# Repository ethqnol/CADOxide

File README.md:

# CADoxide

**CADoxide** is a high-performance, open-core electronic design automation (EDA) and PCB CAD suite built from the ground up for modern hardware engineering. It combines a **100% Pure Rust WebAssembly frontend**, an **instanced WebGL2/GPU Signed Distance Field (SDF) graphics engine**, an **in-browser Design Rule Check (DRC) engine**, an **RS-274X Gerber & Excellon CAM exporter**, an **IPC-standard component footprint library**, and **geometric vector diffing**, with a **distributed Axum cloud backend** and a **Tauri v2 desktop core**.

All JavaScript/TypeScript and React layers have been eliminated: everything from streaming KiCad S-expression parsing, interactive track routing, via/pad placement, polygon zone rendering, real-time clearance rule verification, and CAM Gerber generation down to GPU draw dispatch and reactive DOM management runs in compiled, memory-safe native Rust and WebAssembly.

---

## Key Capabilities & Purpose

- **Interactive In-Browser & Desktop PCB CAD:**
  - Route tracks with 45° angle snapping, posture flipping (`/`), and interactive length tuning.
  - Place plated through-hole vias, pads, lines, arcs, circles, rectangles, text, and dimension callouts.
  - Define, preview, and render filled copper zones, thermal reliefs, and keepouts with customizable fill modes.
  - Configurable grid snapping ($0.05\text{ mm}$ to $2.54\text{ mm}$, mils, inches) with relative coordinate origins (`Space`) and dual Cartesian/polar HUD readouts.
- **Single-Draw-Call Instanced GPU SDF Engine:**
  - Renders entire complex multi-layer boards (traces, pads, zones, silkscreen, mask, holes) in a single instanced WebGL2 draw call.
  - Sub-pixel vertex-stage Level-of-Detail (LOD) and hardware frustum culling yielding silky-smooth 60+ FPS navigation over boards with 100k+ primitives.
  - Real-time 3D exploded multi-layer stackup orbit mode with true physical Z-height layer separation.
  - Instant GPU net highlighting and impedance/delay signal length probing across all copper layers.
- **Native In-Browser DRC Engine:**
  - Runs deep geometric clearance, minimum track width, drill hole clearance, short-circuit, and unconnected net audits directly in client-side Rust WebAssembly.
  - Visual error markers on the canvas with click-to-focus camera navigation and rule severity filtering.
- **RS-274X Gerber & Excellon Drill CAM Exporter:**
  - Client-side production-grade Gerber export for all copper, silkscreen, and solder mask layers (with automatic pad expansion aperture calculation) alongside standard NC Excellon drill files.
- **Built-in IPC Standard Footprint & Component Library:**
  - Ready-to-place standard SMD and THT footprints (0402, 0603, 0805, 1206 passives, SOT-23, SOIC-8, TSSOP-16, QFP-48, QFN-32, USB-C, 0.1" headers) with live SVG preview generator and automatic reference designator incrementing.
- **Hardware Collaboration, Vector Diffing & Review:**
  - Spatial quantized geometric diffing between PCB revisions ($R_A$ vs. $R_B$) with color-coded additions/removals and interactive split-wipe slider inspection.
  - Persistent redline review pins, threaded annotations, and synchronized design reviews backed by SQLite / PostgreSQL.
- **Dual Deployment — Desktop Native & Cloud Platform:**
  - Run natively as a lightweight desktop application via **Tauri v2** with direct filesystem and OS `kicad-cli` integrations.
  - Deploy as a scalable, containerized cloud collaboration hub with Axum, Tokio worker pools, Content-Addressable Storage (CAS), PostgreSQL, Redis, and MinIO.
- **Content-Addressable Storage (CAS):** Hashes PCB file contents and caches rendered layer SVGs and DRC analysis in memory. Cache hits bypass `kicad-cli` execution entirely.
- **Worker Pool & Message Broker:** Compute jobs (DRC verification, PCB SVG rendering, 3D VRML model generation) are pushed to a Tokio `mpsc` channel and scheduled across a bounded `Semaphore` worker pool.
- **Centralized Component Library (`parts_library`):**
  - Manages Manufacturer Part Numbers (MPNs), footprints, symbols, lifecycle statuses (`ACTIVE`, `NRND`, `OBSOLETE`), and cached DigiKey/Mouser inventory and unit pricing.
  - Accessible via the **Parts & BOM** tab in the UI with instant search filtering.
- **Collaborative Redline Review Threads:**
  - Review pins dropped at precise board coordinates $(X, Y\text{ mm})$ persist to SQLite (`review_threads`, `review_messages`) and sync in real time across clients.
  - Supports marking threads as **Resolved / Open** and jumping the GPU camera directly to annotations or DRC violations.

---

## Repository Structure

```
CADoxide/
├── crates/
│   └── cadoxide-wasm/           # 100% Pure Rust WASM Frontend & GPU Shader Engine
│       ├── Cargo.toml           # Configured for wasm32-unknown-unknown (zero JS dependencies)
│       └── src/
│           ├── gl_renderer.rs   # WebGL2 Instanced SDF Engine, LOD culling, 3D orbit
│           ├── parser.rs        # KiCad S-expression parser, O(1) spatial grid, vector diff
│           ├── drc_engine.rs    # Client-side clearance, track width, & drill DRC audit engine
│           ├── gerber_exporter.rs # RS-274X Gerber & Excellon drill CAM exporter
│           ├── footprint_library.rs # IPC standard footprint templates & SVG previews
│           ├── overlay_renderer.rs  # Crosshairs, ratsnest, coordinate grid & zone overlays
│           └── lib.rs           # WebAssembly entry, DOM controller, CAD tools & review pins
├── server/                      # Distributed Axum Cloud Server
│   ├── Cargo.toml
│   └── src/
│       └── main.rs              # CAS cache, worker semaphore, SQLite DB, REST & static API
├── src-tauri/                   # Tauri v2 Desktop Core
│   ├── Cargo.toml
│   ├── tauri.conf.json          # Configured to load pure-Rust bundle from ../public
│   └── src/
│       ├── lib.rs               # Desktop invoke handlers
│       └── commands/
│           ├── kicad.rs         # Subprocess pipelines (PCB, Sch, DRC, 3D VRML)
│           ├── git.rs           # Git log and revision tracking
│           └── db.rs            # Local review thread database
├── public/                      # Static web distribution directory
│   ├── index.html               # Pure-Rust WASM bootstrapper (zero React/JS)
│   ├── styles.css               # Pre-compiled standalone Tailwind CSS
│   ├── wasm/                    # Compiled release WebAssembly artifacts
│   │   ├── cadoxide_wasm_bg.wasm
│   │   └── cadoxide_wasm.js
│   └── samples/                 # KiCad sample boards, SVGs, DRC reports, and 3D VRML models
│       ├── complex_hierarchy/
│       ├── complex_hierarchy_revB/
│       └── cm5_minima/
├── docker-compose.yml           # Self-hosted stack (NGINX, Axum, KiCad worker, Postgres, Redis, MinIO)
├── nginx.conf                   # Reverse proxy and least-connections load balancer
├── migrations/                  # PostgreSQL database migrations
│   └── 001_init.sql
└── package.json                 # Rust WASM and server orchestration scripts
```

---

## Quick Start & Build Instructions

### Prerequisites
- **Rust Toolchain:** `rustup target add wasm32-unknown-unknown`
- **wasm-bindgen CLI:** `cargo install wasm-bindgen-cli --version 0.2.127`
- **KiCad CLI:** `kicad-cli` (v8 or v10 recommended for headless exports)

### 1. Build the Pure-Rust WASM Engine
Compile the release WebAssembly bundle and bindgen glue:
```bash
npm run build:wasm
```
*(Or directly via cargo:)*
```bash
cargo build --manifest-path crates/cadoxide-wasm/Cargo.toml --target wasm32-unknown-unknown --release
wasm-bindgen --target web --no-typescript --out-dir public/wasm crates/cadoxide-wasm/target/wasm32-unknown-unknown/release/cadoxide_wasm.wasm
```

### 2. Run the Rust Axum Server (Web Mode)
The Axum server serves both the REST API (`/api/*`) and the pure-Rust WebAssembly frontend from `public/`:
```bash
npm run server
# Or: cargo run --manifest-path server/Cargo.toml
```
Open **`http://localhost:8080`** in your browser.

### 3. Build & Run Desktop App (Tauri v2)
To run or package CADoxide as a native cross-platform desktop application:

```bash
# Run desktop dev mode
npx @tauri-apps/cli dev

# Build release desktop bundle (.AppImage / .deb / .dmg / .msi)
npx @tauri-apps/cli build
```

> **Note for Linux:** Ensure WebKitGTK and libsoup development libraries are installed (`webkit2gtk4.1-devel` and `libsoup3-devel` on Fedora; `libwebkit2gtk-4.1-dev` and `libsoup-3.0-dev` on Debian/Ubuntu).

### 4. Run Automated Rust Unit Tests
Execute the unit tests verifying KiCad parsing, 4-layer copper extraction, $O(1)$ spatial grid lookups, and geometric vector diffs:
```bash
cargo test --manifest-path crates/cadoxide-wasm/Cargo.toml --lib
```

### 5. Deploy Full Cloud Microservices
To spin up the distributed backend with NGINX load balancing, PostgreSQL, Redis, and MinIO:
```bash
docker compose up -d
```

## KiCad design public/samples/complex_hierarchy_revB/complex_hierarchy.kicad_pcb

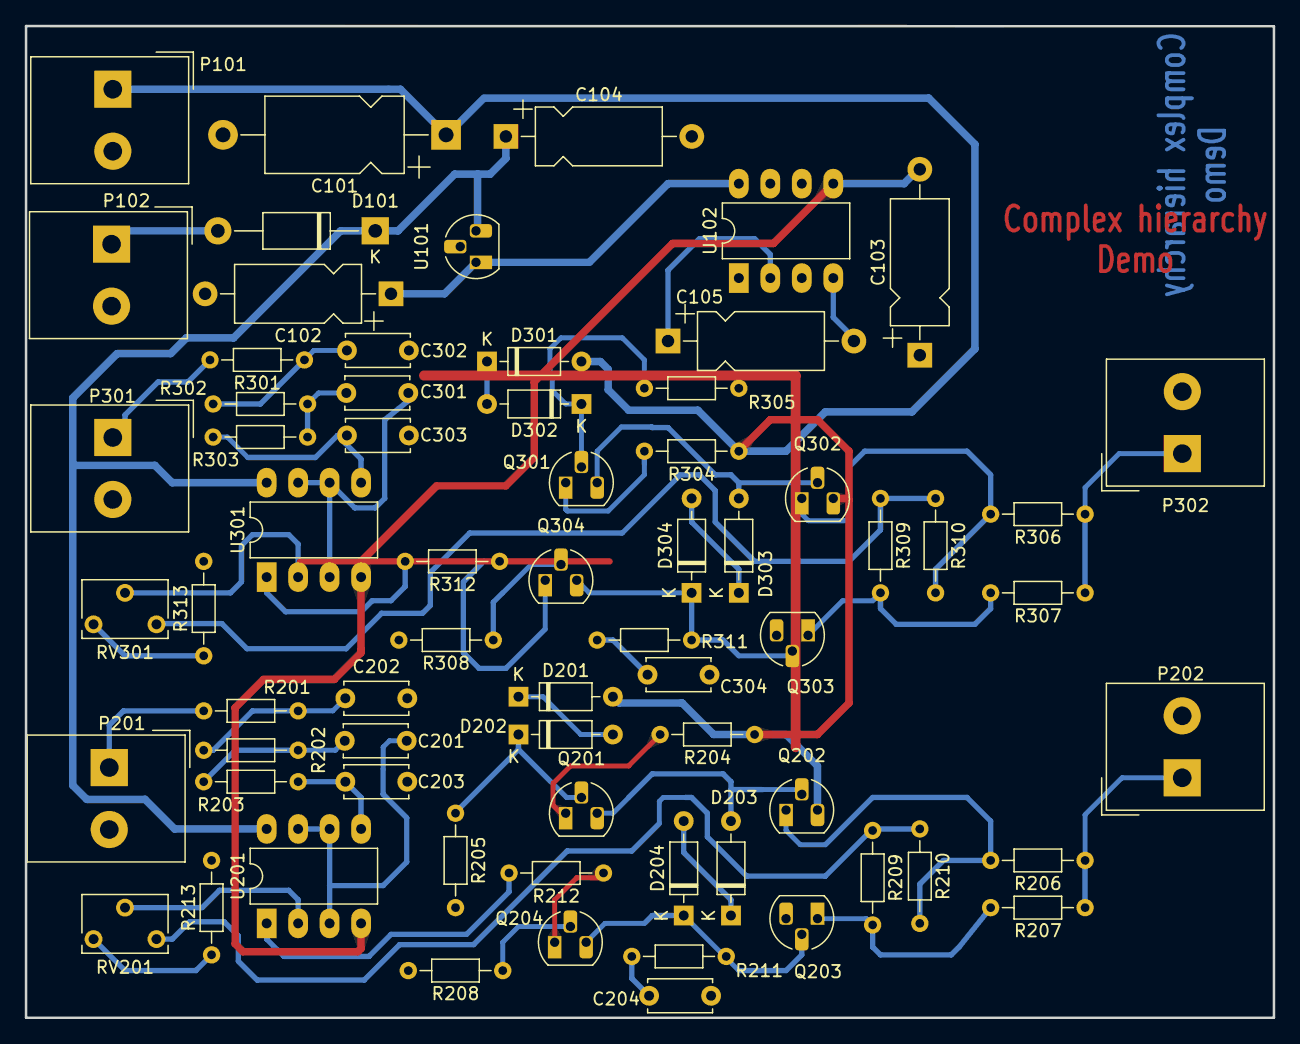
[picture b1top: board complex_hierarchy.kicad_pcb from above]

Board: 2 copper layers, 100.7 x 80.0 mm, 68 parts (0 on the bottom side), 50 nets.

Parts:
C101: 47uF/63V; CP_Axial_L11.0mm_D6.0mm_P18.00mm_Horizontal
C102: 47uF; CP_Axial_L10.0mm_D4.5mm_P15.00mm_Horizontal
C103, C105: 10uF; CP_Axial_L10.0mm_D4.5mm_P15.00mm_Horizontal
C104: 47uF/20V; CP_Axial_L10.0mm_D4.5mm_P15.00mm_Horizontal
C201, C301: 15nF; C_Disc_D5.0mm_W2.5mm_P5.00mm
C202, C302: 150nF; C_Disc_D5.0mm_W2.5mm_P5.00mm
C203, C303: 4.7nF; C_Disc_D5.0mm_W2.5mm_P5.00mm
C204, C304: 820pF; C_Disc_D5.0mm_W2.5mm_P5.00mm
D101: 1N4007; D_DO-41_SOD81_P12.70mm_Horizontal
D201, D202, D203, D204, D301, D302, D303, D304: 1N4148; D_DO-35_SOD27_P7.62mm_Horizontal
P101, P102, P201, P202, P301, P302: CONN_2; Altech_AK300_1x02_P5.00mm_45-Degree
Q201, Q203, Q301, Q303: MPSA92; TO-92_HandSolder
Q202, Q204, Q302, Q304: MPSA42; TO-92_HandSolder
R201, R208, R212, R301, R308, R312: 1K; R_Axial_DIN0204_L3.6mm_D1.6mm_P7.62mm_Horizontal
R202, R203, R302, R303: 22K; R_Axial_DIN0204_L3.6mm_D1.6mm_P7.62mm_Horizontal
R204, R304: 470; R_Axial_DIN0204_L3.6mm_D1.6mm_P7.62mm_Horizontal
R205, R209, R210, R305, R309, R310: 220K; R_Axial_DIN0204_L3.6mm_D1.6mm_P7.62mm_Horizontal
R206, R207, R306, R307: 47; R_Axial_DIN0204_L3.6mm_D1.6mm_P7.62mm_Horizontal
R211, R311: 5,6K; R_Axial_DIN0204_L3.6mm_D1.6mm_P7.62mm_Horizontal
R213, R313: 4,7K; R_Axial_DIN0204_L3.6mm_D1.6mm_P7.62mm_Horizontal
RV201, RV301: 4,7K; Potentiometer_Bourns_3266W_Vertical
U101: 78L05; TO-92_HandSolder
U102: ICL7660; DIP-8_W7.62mm_LongPads
U201, U301: LM358N; DIP-8_W7.62mm_LongPads

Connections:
+12V: C104.1, D101.1 (K), U101.3 (VI), U201.8 (V+), U301.8 (V+)
-VAA: C103.2, U102.5 (VOUT), U201.4 (V-), U301.4 (V-)
/12Vext: D101.2 (A), P102.1
/ampli_ht_horizontal/PIEZO_IN: P301.1, R301.2
/ampli_ht_horizontal/PIEZO_OUT: P302.1, R306.1, R307.1
/ampli_ht_horizontal/S_OUT+: R309.1, R310.1, RV301.3
/ampli_ht_horizontal/Vpil_0_3,3V: C301.1, U301.3 (+), U301.6 (-), U301.7
/ampli_ht_vertical/PIEZO_IN: P201.1, R201.2
/ampli_ht_vertical/PIEZO_OUT: P202.1, R206.1, R207.1
/ampli_ht_vertical/S_OUT+: R209.1, R210.1, RV201.3
/ampli_ht_vertical/Vpil_0_3,3V: C201.1, U201.3 (+), U201.6 (-), U201.7
GND: C101.2, C102.2, C103.1, C104.2, C202.2, C203.2, C204.2, C302.2, C303.2, C304.2, P101.2 (PM), P102.2 (PM), P201.2 (PM), P202.2 (PM), P301.2 (PM), P302.2 (PM), Q203.3 (C), Q303.3 (C), R205.2, R208.2, R213.2, R305.2, R308.2, R313.2, U101.2 (GND), U102.3 (GND)
HT: C101.1, D201.2 (A), D301.2 (A), P101.1, Q202.3 (C), Q302.3 (C), R204.1, R304.1
unnamed: C201.2, R202.1, R203.2
unnamed: C202.1, R201.1, R202.2
unnamed: C204.1, R211.2
unnamed: C301.2, R302.1, R303.2
unnamed: C302.1, R301.1, R302.2
unnamed: C304.1, R311.2
unnamed: D201.1 (K), D202.2 (A)
unnamed: D202.1 (K), Q201.2 (B), R205.1
unnamed: D203.2 (A), Q201.3 (C), Q202.2 (B)
unnamed: D203.1 (K), D204.2 (A)
unnamed: D204.1 (K), Q203.2 (B), Q204.3 (C), R211.1
unnamed: D301.1 (K), D302.2 (A)
unnamed: D302.1 (K), Q301.2 (B), R305.1
unnamed: D303.2 (A), Q301.3 (C), Q302.2 (B)
unnamed: D303.1 (K), D304.2 (A)
unnamed: D304.1 (K), Q303.2 (B), Q304.3 (C), R311.1
unnamed: Q201.1 (E), R204.2
unnamed: Q202.1 (E), R206.2, R210.2
unnamed: Q203.1 (E), R207.2, R209.2
unnamed: Q204.2 (B), R208.1
unnamed: Q204.1 (E), R212.1
unnamed: Q301.1 (E), R304.2
unnamed: Q302.1 (E), R306.2, R310.2
unnamed: Q303.1 (E), R307.2, R309.2
unnamed: Q304.2 (B), R308.1
unnamed: Q304.1 (E), R312.1
unnamed: R212.2, U201.1
unnamed: R213.1, RV201.1
unnamed: R312.2, U301.1
unnamed: R313.1, RV301.1
unnamed: C105.1, U102.2 (CAP+)
unnamed: C105.2, U102.4 (CAP-)
unnamed: RV201.2, U201.2 (-)
unnamed: C203.1, R203.1, U201.5 (+)
unnamed: RV301.2, U301.2 (-)
unnamed: C303.1, R303.1, U301.5 (+)
VCC: C102.1, U101.1 (VO), U102.8 (V+)
